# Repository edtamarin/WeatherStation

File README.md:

# WeatherStation
Weather station for a smart home framework, based on ESP8266 and BME280.
## Features
  * Two status LEDs
  * MQTT control
  * OTA updates
  * Temperature, pressure and humidity data
## Hardware
The PCN for the station is designed in KiCad.

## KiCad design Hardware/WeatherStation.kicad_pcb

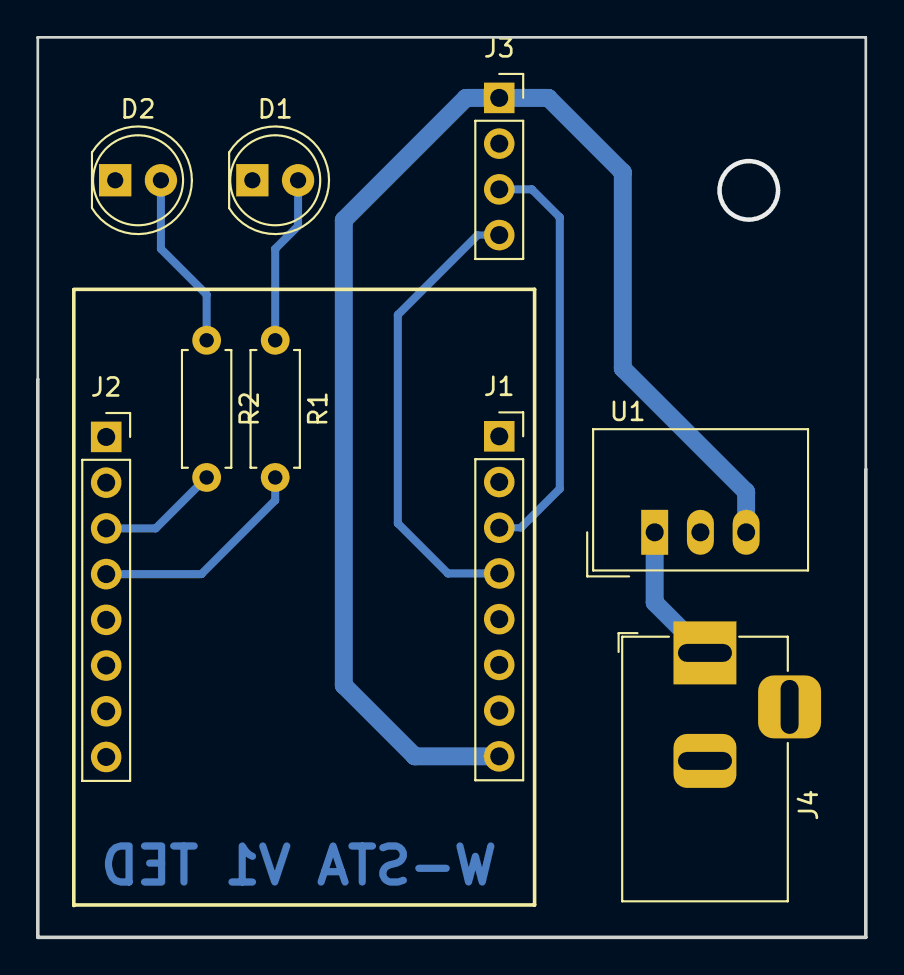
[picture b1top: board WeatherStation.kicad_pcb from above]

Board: 2 copper layers, 46.0 x 50.0 mm, 9 parts (0 on the bottom side), 9 nets.

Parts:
D1, D2: LED; LED_D5.0mm
J1, J2: Conn_01x08; PinSocket_1x08_P2.54mm_Vertical
J3: Conn_01x04; PinSocket_1x04_P2.54mm_Vertical
J4: Barrel_Jack_Switch; BarrelJack_Horizontal
R1, R2: R; R_Axial_DIN0207_L6.3mm_D2.5mm_P7.62mm_Horizontal
U1: TSR_1-2450; Converter_DCDC_TRACO_TSR-1_THT

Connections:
+5V: J1.8, J3.1, U1.3
+VDC: J4.1, U1.1
GND: D1.1, D2.1, J1.7, J3.2, J4.2, U1.2
unnamed: D1.2, R1.1
unnamed: D2.2, R2.1
unnamed: J2.3, R2.2
unnamed: J2.4, R1.2
SCL: J1.3, J3.3
SDA: J1.4, J3.4

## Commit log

2018-11-25 BME sensor connected to MQTT
2018-11-26 Add hardware
2018-11-28 Hardware changes
    Added power and status LED, removed 1 screw hole
2018-11-28 Implemented LEDs
2019-01-09 OTA update + MQTT integration
